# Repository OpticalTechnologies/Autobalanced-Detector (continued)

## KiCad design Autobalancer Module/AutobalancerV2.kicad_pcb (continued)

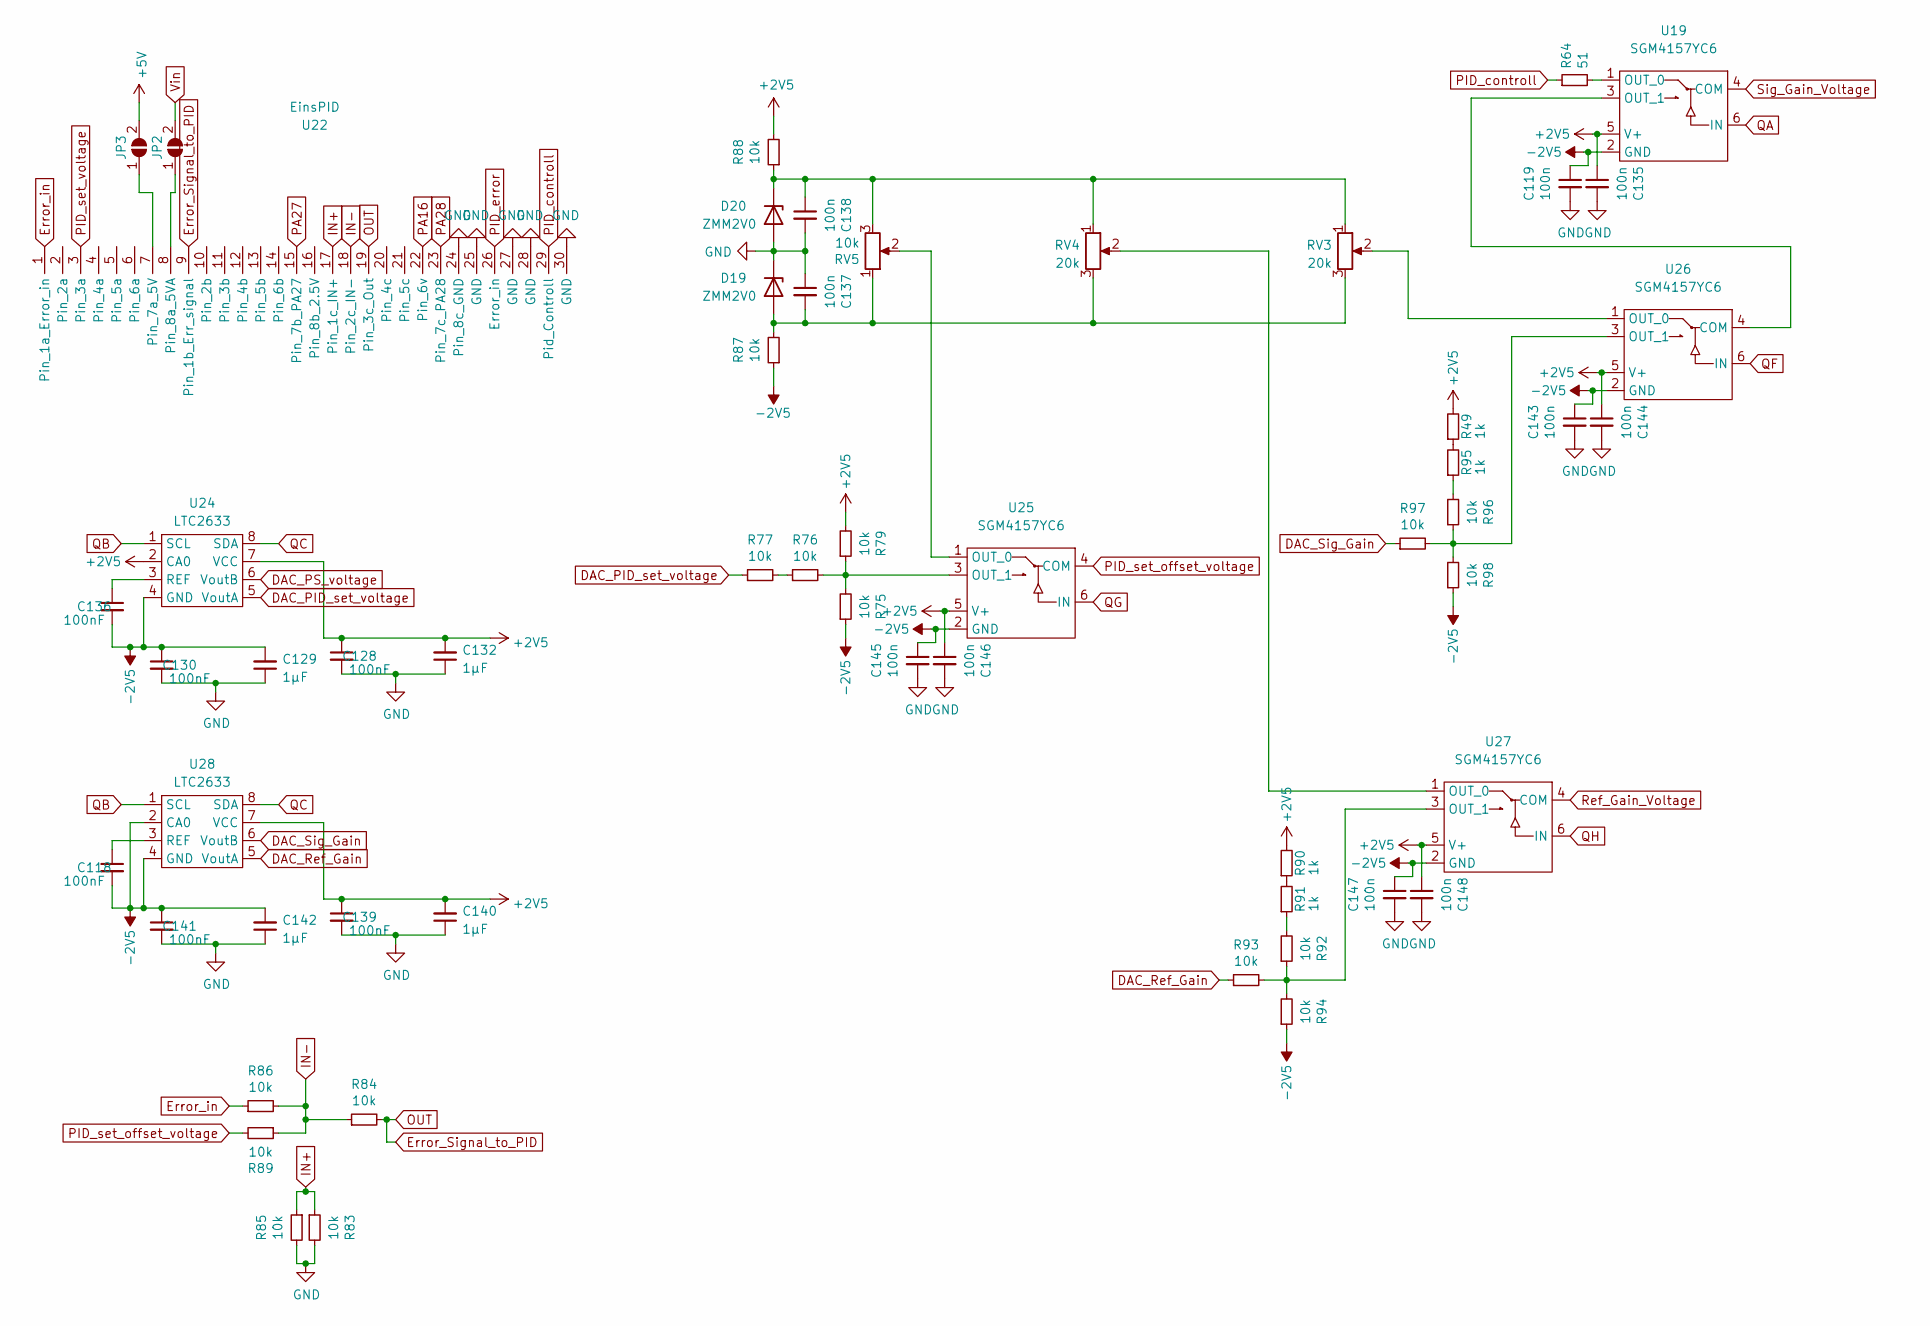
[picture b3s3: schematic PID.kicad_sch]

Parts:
C118, C128, C130, C136, C139, C141: 100nF; C_0402_1005Metric; LCSC C307331
C119, C135, C137, C138, C143, C144, C145, C146, C147, C148: 100n; C_0402_1005Metric; LCSC C1525
C129, C132, C140, C142: 1µF; C_0402_1005Metric; LCSC C52923
D19, D20: ZMM2V0; D_MiniMELF; LCSC C8079
JP2, JP3: SolderJumper_2_Open; 0603_solderbridge
R49, R90, R91, R95: 1k; R_0402_1005Metric; LCSC C11702
R64: 51; R_0402_1005Metric; LCSC C25125
R75, R76, R77, R79, R83, R84, R85, R86, R87, R88, R89, R92, R93, R94, R96, R97, R98: 10k; R_0402_1005Metric; LCSC C25744
RV3, RV4: 20k; Potentiometer_Bourns_3296W_Vertical
RV5: 10k; Potentiometer_Bourns_3296W_Vertical
U19, U25, U26, U27: SGM4157YC6; SC-60; LCSC C124895
U22: EinsPID
U24, U28: LTC2633; SOT-23-8

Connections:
+2V5: C128.1, C132.2, C135.1, C139.1, C140.2, C144.1, C146.1, C148.1, R49.2, R79.2, R88.2, R90.2, U19.5 (V+), U24.2 (CA0), U24.7 (VCC), U25.5 (V+), U26.5 (V+), U27.5 (V+), U28.7 (VCC); also elsewhere on the board
+5V: JP3.2 (B); also elsewhere on the board
-2V5: C118.2, C119.1, C129.2, C130.1, C136.2, C141.1, C142.2, C143.1, C145.1, C147.1, R75.1, R87.1, R94.1, R98.1, U19.2 (GND), U24.4 (GND), U25.2 (GND), U26.2 (GND), U27.2 (GND), U28.2 (CA0), U28.4 (GND); also elsewhere on the board
DAC_PID_set_voltage: R77.1, U24.5 (VoutA)
DAC_PS_voltage: U24.6 (VoutB); also elsewhere on the board
DAC_Ref_Gain: R93.1, U28.5 (VoutA)
DAC_Sig_Gain: R97.1, U28.6 (VoutB)
Error_Signal_to_PID: R84.2, U22.9 (Pin_1b_Err_signal), U22.19 (Pin_3c_Out)
Error_in: R86.1, U22.1 (Pin_1a_Error_in)
GND: C119.2, C128.2, C129.1, C130.2, C132.1, C135.2, C137.1, C138.2, C139.2, C140.1, C141.2, C142.1, C143.2, C144.2, C145.2, C146.2, C147.2, C148.2, D19.1 (K), D20.2 (A), R83.2, R85.2, U22.24 (Pin_8c_GND), U22.25 (GND), U22.27 (GND), U22.28 (GND), U22.30 (GND); also elsewhere on the board
IN+: R83.1, R85.1, U22.17 (Pin_1c_IN+)
IN-: R84.1, R86.2, R89.1, U22.18 (Pin_2c_IN-)
unnamed: C118.1, U28.3 (REF)
unnamed: C136.1, U24.3 (REF)
unnamed: C137.2, D19.2 (A), R87.2, RV3.3, RV4.3, RV5.1
unnamed: C138.1, D20.1 (K), R88.1, RV3.1, RV4.1, RV5.3
unnamed: JP2.1 (A), U22.8 (Pin_8a_5VA)
unnamed: JP3.1 (A), U22.7 (Pin_7a_5V)
unnamed: R49.1, R95.2
unnamed: R64.2, U19.1 (OUT_0)
unnamed: R75.2, R76.2, R79.1, U25.3 (OUT_1)
unnamed: R76.1, R77.2
unnamed: R90.1, R91.2
unnamed: R91.1, R92.2
unnamed: R92.1, R93.2, R94.2, U27.3 (OUT_1)
unnamed: R95.1, R96.2
unnamed: R96.1, R97.2, R98.2, U26.3 (OUT_1)
unnamed: RV3.2, U26.1 (OUT_0)
unnamed: RV4.2, U27.1 (OUT_0)
unnamed: RV5.2, U25.1 (OUT_0)
unnamed: U19.3 (OUT_1), U26.4 (COM)
PA16: U22.22 (Pin_6v); also elsewhere on the board
PA27: U22.15 (Pin_7b_PA27); also elsewhere on the board
PA28: U22.23 (Pin_7c_PA28); also elsewhere on the board
PID_controll: R64.1, U22.29 (Pid_Controll)
PID_error: U22.26 (Error_in); also elsewhere on the board
PID_set_offset_voltage: R89.2, U25.4 (COM)
PID_set_voltage: U22.3 (Pin_3a)
QA: U19.6 (IN); also elsewhere on the board
QB: U24.1 (SCL), U28.1 (SCL); also elsewhere on the board
QC: U24.8 (SDA), U28.8 (SDA); also elsewhere on the board
QF: U26.6 (IN); also elsewhere on the board
QG: U25.6 (IN); also elsewhere on the board
QH: U27.6 (IN); also elsewhere on the board
Ref_Gain_Voltage: U27.4 (COM); also elsewhere on the board
Sig_Gain_Voltage: U19.4 (COM); also elsewhere on the board
Vin: JP2.2 (B); also elsewhere on the board

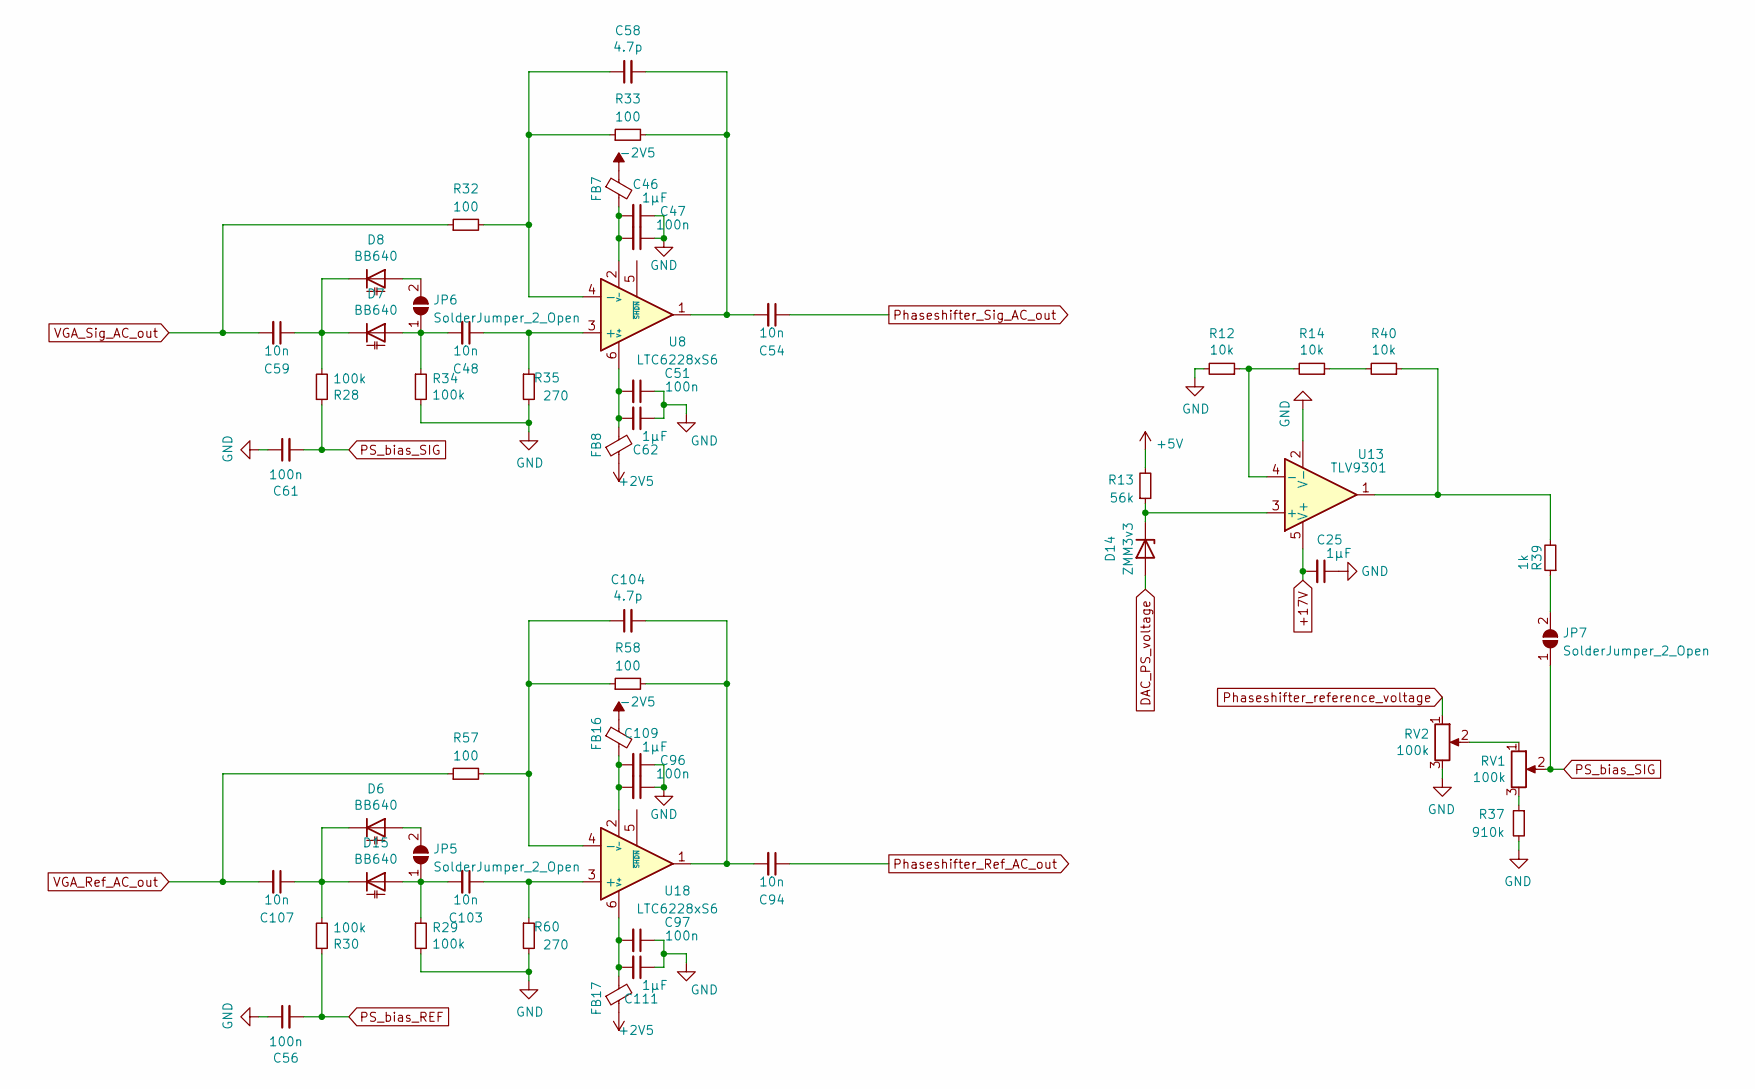
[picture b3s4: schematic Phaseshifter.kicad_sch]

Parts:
C25, C46, C62, C109, C111: 1µF; C_0402_1005Metric; LCSC C52923
C47, C51, C56, C61, C96, C97: 100n; C_0402_1005Metric; LCSC C1525
C48, C54, C59, C94, C103, C107: 10n; C_0402_1005Metric; LCSC C15195
C58, C104: 4.7p; C_0402_1005Metric; LCSC C1569
D6, D7, D8, D15: BB640; D_SOD-323F; LCSC C150932
D14: ZMM3v3; D_MiniMELF; LCSC C8056
FB7, FB8, FB16, FB17: Ferrite_Bead_Small; L_0603_1608Metric; LCSC C1002
JP5, JP6, JP7: SolderJumper_2_Open; 0603_solderbridge
R12, R14, R40: 10k; R_0402_1005Metric; LCSC C25744
R13: 56k; R_0402_1005Metric; LCSC C25796
R28, R29, R30, R34: 100k; R_0402_1005Metric; LCSC C25741
R32, R33, R57, R58: 100; R_0402_1005Metric; LCSC C25076
R35, R60: 270; R_0402_1005Metric; LCSC C25099
R37: 910k; R_0402_1005Metric; LCSC C25572
R39: 1k; R_0402_1005Metric; LCSC C11702
RV1, RV2: 100k; Potentiometer_Bourns_3296W_Vertical
U8, U18: LTC6228xS6; TSOT-23-6
U13: TLV9301; SOT-23-5; Mouser 595-TLV9301IDBVR

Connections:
+2V5: FB8.1, FB17.1; also elsewhere on the board
+5V: R13.2; also elsewhere on the board
+17V: C25.2, U13.5 (V+); also elsewhere on the board
-2V5: FB7.1, FB16.1; also elsewhere on the board
DAC_PS_voltage: D14.2 (A); also elsewhere on the board
GND: C25.1, C46.1, C47.1, C51.1, C56.1, C61.1, C62.1, C96.1, C97.1, C109.1, C111.1, R12.2, R29.2, R34.2, R35.2, R37.2, R60.2, RV2.3, U13.2 (V-); also elsewhere on the board
unnamed: C46.2, C47.2, FB7.2, U8.2 (V-)
unnamed: C48.1, R35.1, U8.3 (+)
unnamed: C48.2, D7.2 (A), JP6.1 (A), R34.1
unnamed: C51.2, C62.2, FB8.2, U8.6 (V+)
unnamed: C54.2, C58.2, R33.2, U8.1
unnamed: C58.1, R32.2, R33.1, U8.4 (-)
unnamed: C59.1, D7.1 (K), D8.1 (K), R28.2
unnamed: C103.1, R60.1, U18.3 (+)
unnamed: C103.2, D15.2 (A), JP5.1 (A), R29.1
unnamed: C104.1, R57.2, R58.1, U18.4 (-)
unnamed: C94.2, C104.2, R58.2, U18.1
unnamed: C107.1, D6.1 (K), D15.1 (K), R30.2
unnamed: C96.2, C109.2, FB16.2, U18.2 (V-)
unnamed: C97.2, C111.2, FB17.2, U18.6 (V+)
unnamed: D6.2 (A), JP5.2 (B)
unnamed: D8.2 (A), JP6.2 (B)
unnamed: D14.1 (K), R13.1, U13.3 (+)
unnamed: JP7.2 (B), R39.1
unnamed: R12.1, R14.2, U13.4 (-)
unnamed: R14.1, R40.2
unnamed: R37.1, RV1.3
unnamed: R39.2, R40.1, U13.1
unnamed: RV1.1, RV2.2
PS_bias_REF: C56.2, R30.1; also elsewhere on the board
PS_bias_SIG: C61.2, JP7.1 (A), R28.1, RV1.2
Phaseshifter_Ref_AC_out: C94.1; also elsewhere on the board
Phaseshifter_Sig_AC_out: C54.1; also elsewhere on the board
Phaseshifter_reference_voltage: RV2.1; also elsewhere on the board
VGA_Ref_AC_out: C107.2, R57.1; also elsewhere on the board
VGA_Sig_AC_out: C59.2, R32.1; also elsewhere on the board

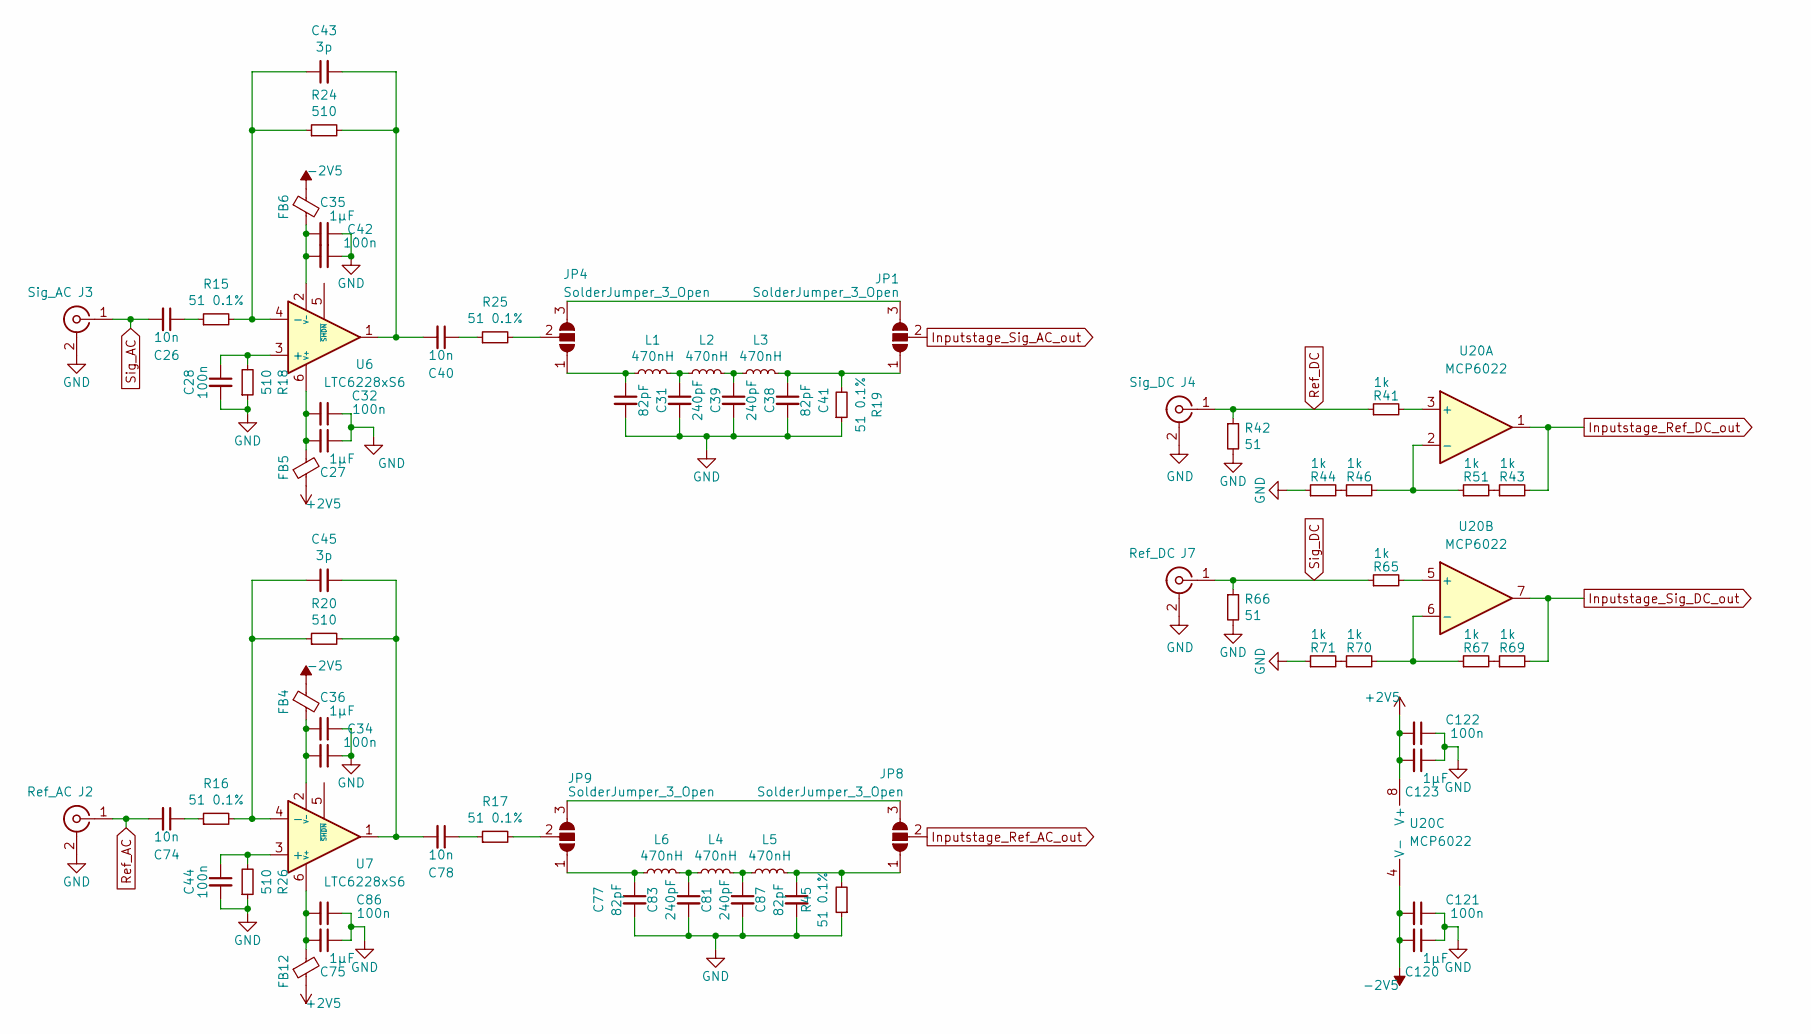
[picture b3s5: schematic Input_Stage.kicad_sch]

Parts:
C26, C40, C74, C78: 10n; C_0402_1005Metric; LCSC C15195
C27, C35, C36, C75, C120, C123: 1µF; C_0402_1005Metric; LCSC C52923
C28, C32, C34, C42, C44, C86, C121, C122: 100n; C_0402_1005Metric; LCSC C1525
C31, C41, C77, C87: 82pF; C_0402_1005Metric; LCSC C162123
C38, C39, C81, C83: 240pF; C_0603_1608Metric; LCSC C519400
C43, C45: 3p; C_0402_1005Metric; LCSC C88891
FB4, FB5, FB6, FB12: Ferrite_Bead_Small; L_0603_1608Metric; LCSC C1002
J2: Ref_AC; SMA_edge
J3: Sig_AC; SMA_edge
J4: Sig_DC; SMA_edge
J7: Ref_DC; SMA_edge
JP1, JP4, JP8, JP9: SolderJumper_3_Open; 0603_solderbridge3
L1, L2, L3, L4, L5, L6: 470nH; AISC-0805_Inductor; LCSC C127457
R15, R16, R17, R19, R25, R45: 51 0.1%; R_0402_1005Metric; LCSC C445570
R18, R20, R24, R26: 510; R_0402_1005Metric; LCSC C25170
R41, R43, R44, R46, R51, R65, R67, R69, R70, R71: 1k; R_0402_1005Metric; LCSC C11702
R42, R66: 51; R_0402_1005Metric; LCSC C25125
U6, U7: LTC6228xS6; TSOT-23-6
U20: MCP6022; SOIC-8_3.9x4.9mm_P1.27mm; LCSC C57639

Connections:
+2V5: C122.2, C123.2, FB5.1, FB12.1, U20.8 (V+); also elsewhere on the board
-2V5: C120.2, C121.2, FB4.1, FB6.1, U20.4 (V-); also elsewhere on the board
GND: C27.1, C28.2, C31.2, C32.1, C34.1, C35.1, C36.1, C38.2, C39.2, C41.2, C42.1, C44.2, C75.1, C77.2, C81.2, C83.2, C86.1, C87.2, C120.1, C121.1, C122.1, C123.1, J2.2 (Ext), J3.2 (Ext), J4.2 (Ext), J7.2 (Ext), R18.1, R19.1, R26.1, R42.2, R44.1, R45.1, R66.2, R71.1; also elsewhere on the board
Inputstage_Ref_AC_out: JP8.2 (C); also elsewhere on the board
Inputstage_Ref_DC_out: R43.2, U20.1; also elsewhere on the board
Inputstage_Sig_AC_out: JP1.2 (C); also elsewhere on the board
Inputstage_Sig_DC_out: R69.2, U20.7; also elsewhere on the board
unnamed: C26.1, R15.1
unnamed: C27.2, C32.2, FB5.2, U6.6 (V+)
unnamed: C28.1, R18.2, U6.3 (+)
unnamed: C31.1, JP4.1 (A), L1.1
unnamed: C34.2, C36.2, FB4.2, U7.2 (V-)
unnamed: C35.2, C42.2, FB6.2, U6.2 (V-)
unnamed: C38.1, L2.2, L3.1
unnamed: C39.1, L1.2, L2.1
unnamed: C40.1, R25.1
unnamed: C40.2, C43.2, R24.2, U6.1
unnamed: C41.1, JP1.1 (A), L3.2, R19.2
unnamed: C43.1, R15.2, R24.1, U6.4 (-)
unnamed: C44.1, R26.2, U7.3 (+)
unnamed: C45.1, R16.2, R20.1, U7.4 (-)
unnamed: C45.2, C78.2, R20.2, U7.1
unnamed: C74.1, R16.1
unnamed: C75.2, C86.2, FB12.2, U7.6 (V+)
unnamed: C77.1, JP9.1 (A), L6.2
unnamed: C78.1, R17.1
unnamed: C81.1, L4.1, L5.2
unnamed: C83.1, L4.2, L6.1
unnamed: C87.1, JP8.1 (A), L5.1, R45.2
unnamed: JP1.3 (B), JP4.3 (B)
unnamed: JP4.2 (C), R25.2
unnamed: JP8.3 (B), JP9.3 (B)
unnamed: JP9.2 (C), R17.2
unnamed: R41.2, U20.3 (+)
unnamed: R43.1, R51.2
unnamed: R44.2, R46.1
unnamed: R46.2, R51.1, U20.2 (-)
unnamed: R65.2, U20.5 (+)
unnamed: R67.1, R70.2, U20.6 (-)
unnamed: R67.2, R69.1
unnamed: R70.1, R71.2
Ref_AC: C74.2, J2.1 (In)
Ref_DC: J4.1 (In), R41.1, R42.1
Sig_AC: C26.2, J3.1 (In)
Sig_DC: J7.1 (In), R65.1, R66.1

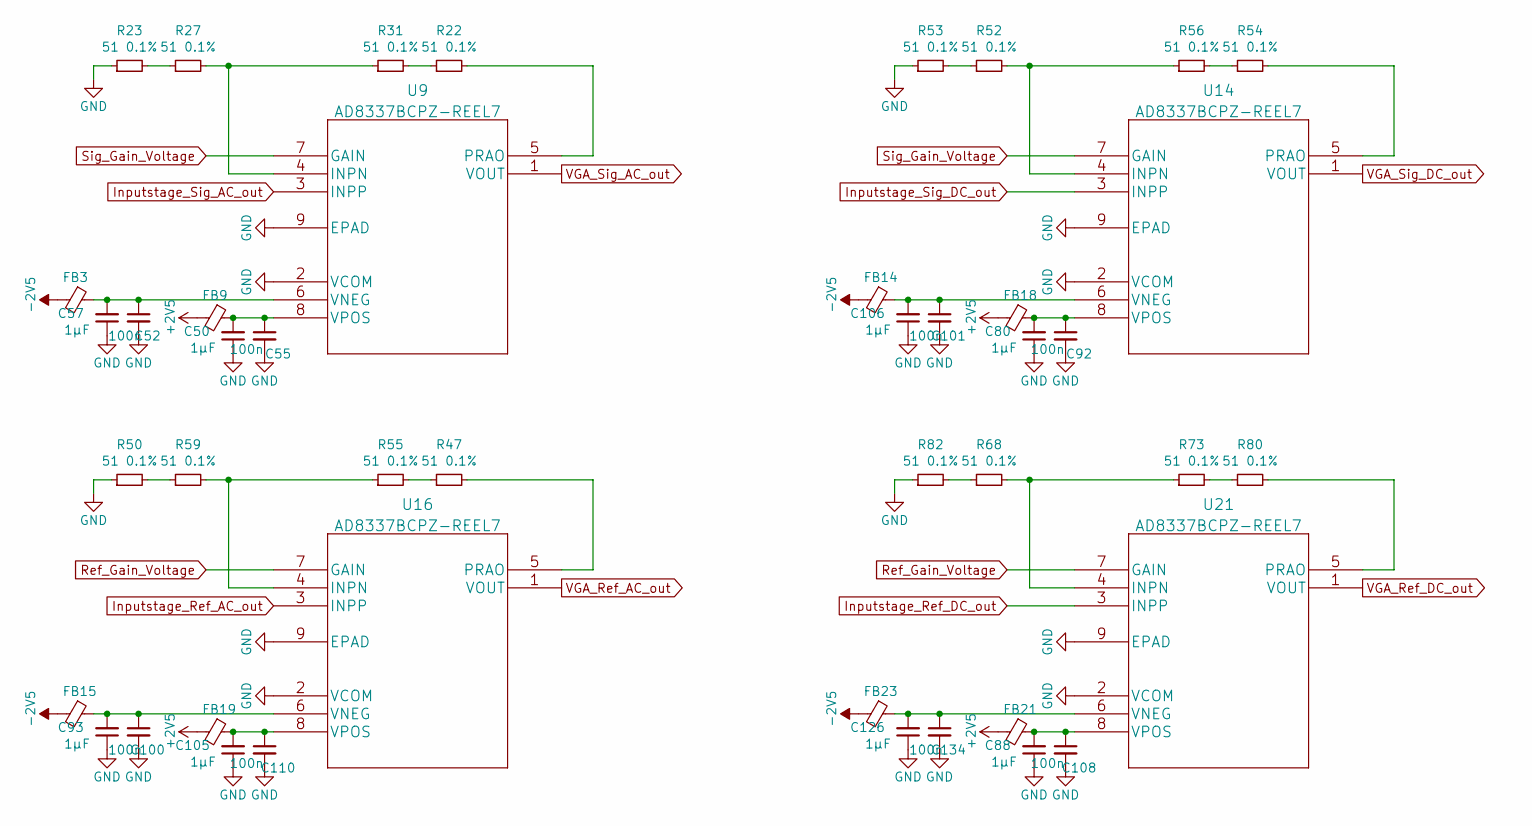
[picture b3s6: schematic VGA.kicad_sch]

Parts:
C50, C57, C80, C88, C93, C105, C106, C126: 1µF; C_0402_1005Metric; LCSC C52923
C52, C55, C92, C100, C101, C108, C110, C134: 100n; C_0402_1005Metric; LCSC C1525
FB3, FB9, FB14, FB15, FB18, FB19, FB21, FB23: Ferrite_Bead_Small; L_0603_1608Metric; LCSC C1002
R22, R23, R27, R31, R47, R50, R52, R53, R54, R55, R56, R59, R68, R73, R80, R82: 51 0.1%; R_0402_1005Metric; LCSC C445570
U9, U14, U16, U21: AD8337BCPZ-REEL7; LFCSP-8-1EP_3x3mm_P0.5mm_EP1.45x1.74mm

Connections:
+2V5: FB9.2, FB18.2, FB19.2, FB21.2; also elsewhere on the board
-2V5: FB3.2, FB14.2, FB15.2, FB23.2; also elsewhere on the board
GND: C50.1, C52.2, C55.2, C57.1, C80.1, C88.1, C92.2, C93.1, C100.2, C101.2, C105.1, C106.1, C108.2, C110.2, C126.1, C134.2, R23.1, R50.1, R53.1, R82.1, U9.2 (VCOM), U9.9 (EPAD), U14.2 (VCOM), U14.9 (EPAD), U16.2 (VCOM), U16.9 (EPAD), U21.2 (VCOM), U21.9 (EPAD); also elsewhere on the board
Inputstage_Ref_AC_out: U16.3 (INPP); also elsewhere on the board
Inputstage_Ref_DC_out: U21.3 (INPP); also elsewhere on the board
Inputstage_Sig_AC_out: U9.3 (INPP); also elsewhere on the board
Inputstage_Sig_DC_out: U14.3 (INPP); also elsewhere on the board
unnamed: C50.2, C55.1, FB9.1, U9.8 (VPOS)
unnamed: C52.1, C57.2, FB3.1, U9.6 (VNEG)
unnamed: C80.2, C92.1, FB18.1, U14.8 (VPOS)
unnamed: C93.2, C100.1, FB15.1, U16.6 (VNEG)
unnamed: C101.1, C106.2, FB14.1, U14.6 (VNEG)
unnamed: C105.2, C110.1, FB19.1, U16.8 (VPOS)
unnamed: C88.2, C108.1, FB21.1, U21.8 (VPOS)
unnamed: C126.2, C134.1, FB23.1, U21.6 (VNEG)
unnamed: R22.1, R31.2
unnamed: R22.2, U9.5 (PRAO)
unnamed: R23.2, R27.1
unnamed: R27.2, R31.1, U9.4 (INPN)
unnamed: R47.1, R55.2
unnamed: R47.2, U16.5 (PRAO)
unnamed: R50.2, R59.1
unnamed: R52.1, R53.2
unnamed: R52.2, R56.1, U14.4 (INPN)
unnamed: R54.1, R56.2
unnamed: R54.2, U14.5 (PRAO)
unnamed: R55.1, R59.2, U16.4 (INPN)
unnamed: R68.1, R82.2
unnamed: R68.2, R73.1, U21.4 (INPN)
unnamed: R73.2, R80.1
unnamed: R80.2, U21.5 (PRAO)
Ref_Gain_Voltage: U16.7 (GAIN), U21.7 (GAIN); also elsewhere on the board
Sig_Gain_Voltage: U9.7 (GAIN), U14.7 (GAIN); also elsewhere on the board
VGA_Ref_AC_out: U16.1 (VOUT); also elsewhere on the board
VGA_Ref_DC_out: U21.1 (VOUT); also elsewhere on the board
VGA_Sig_AC_out: U9.1 (VOUT); also elsewhere on the board
VGA_Sig_DC_out: U14.1 (VOUT); also elsewhere on the board

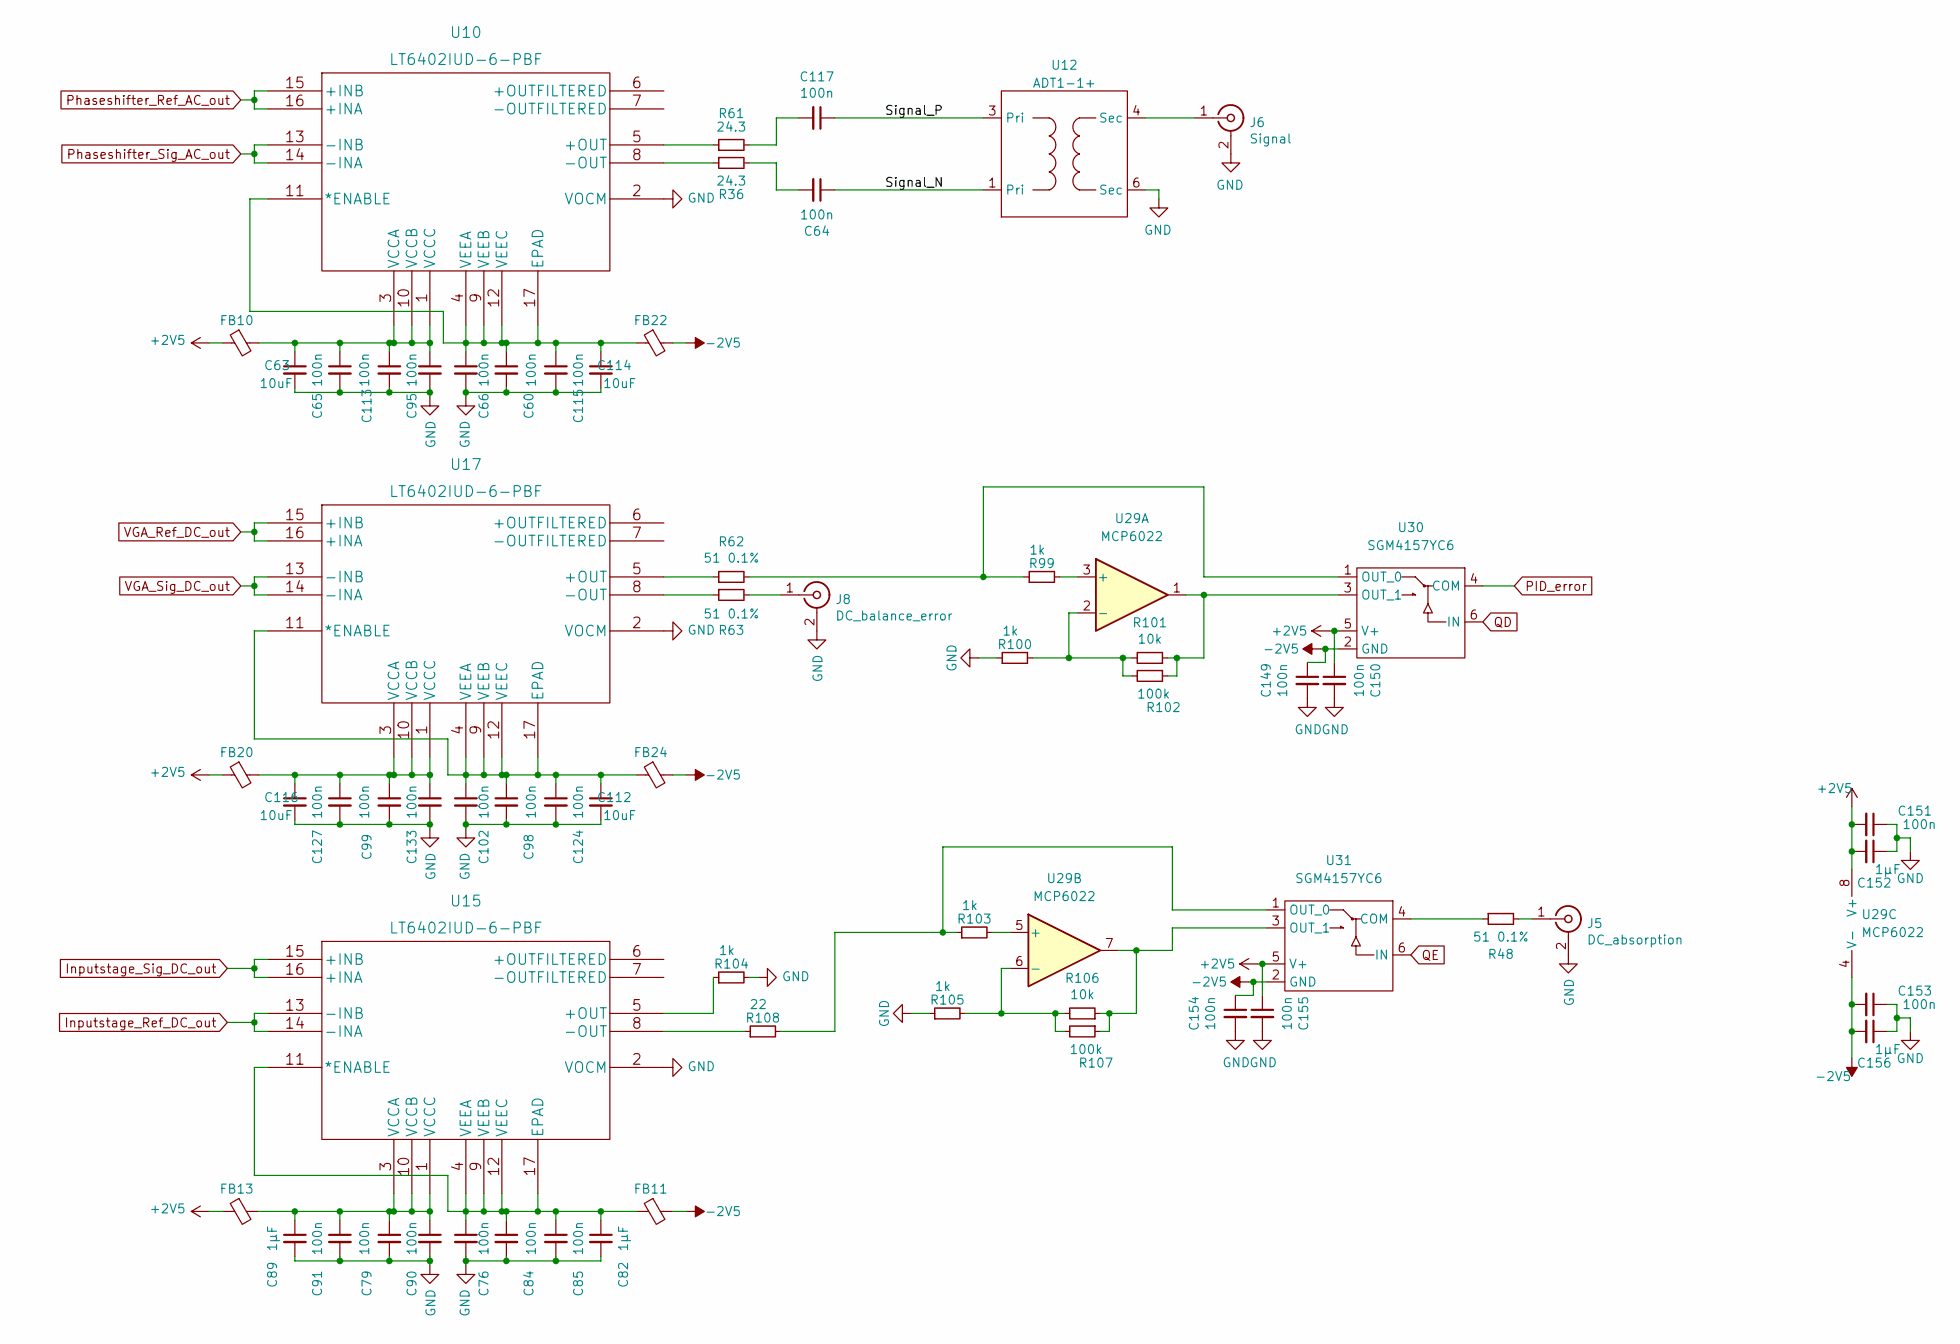
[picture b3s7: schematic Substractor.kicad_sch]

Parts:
C60, C64, C65, C66, C76, C79, C84, C85, C90, C91, C95, C98, C99, C102, C113, C115, C117, C124, C127, C133, C149, C150, C151, C153, C154, C155: 100n; C_0402_1005Metric; LCSC C1525
C63, C112, C114, C116: 10uF; C_1206_3216Metric; LCSC C13585
C82, C89, C152, C156: 1µF; C_0402_1005Metric; LCSC C52923
FB10, FB11, FB13, FB20, FB22, FB24: Ferrite_Bead_Small; L_0603_1608Metric; LCSC C1002
J5: DC_absorption; SMA_edge
J6: Signal; SMA_edge
J8: DC_balance_error; SMA_edge
R36, R61: 24.3; R_0402_1005Metric; LCSC C321400
R48, R62, R63: 51 0.1%; R_0402_1005Metric; LCSC C445570
R99, R100, R103, R104, R105: 1k; R_0402_1005Metric; LCSC C11702
R101, R106: 10k; R_0402_1005Metric; LCSC C25744
R102, R107: 100k; R_0402_1005Metric; LCSC C25741
R108: 22; R_0402_1005Metric
U10, U15, U17: LT6402IUD-6-PBF; QFN-16-1EP_3x3mm_P0.5mm_EP1.45x1.45mm_ThermalVias
U12: ADT1-1+; JLCPCB C2683432
U29: MCP6022; SOIC-8_3.9x4.9mm_P1.27mm; LCSC C57639
U30, U31: SGM4157YC6; SC-60; LCSC C124895

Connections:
+2V5: C150.1, C151.2, C152.2, C155.1, FB10.1, FB13.1, FB20.1, U29.8 (V+), U30.5 (V+), U31.5 (V+); also elsewhere on the board
-2V5: C149.1, C153.2, C154.1, C156.2, FB11.2, FB22.2, FB24.2, U29.4 (V-), U30.2 (GND), U31.2 (GND); also elsewhere on the board
/Substractor/Signal_N: C64.1, U12.1 (Pri)
/Substractor/Signal_P: C117.1, U12.3 (Pri)
GND: C60.2, C63.2, C65.2, C66.2, C76.2, C79.2, C82.2, C84.2, C85.2, C89.2, C90.2, C91.2, C95.2, C98.2, C99.2, C102.2, C112.2, C113.2, C114.2, C115.2, C116.2, C124.2, C127.2, C133.2, C149.2, C150.2, C151.1, C152.1, C153.1, C154.2, C155.2, C156.1, J5.2 (Ext), J6.2 (Ext), J8.2 (Ext), R100.1, R104.2, R105.1, U10.2 (VOCM), U12.6 (Sec), U15.2 (VOCM), U17.2 (VOCM); also elsewhere on the board
Inputstage_Ref_DC_out: U15.13 (-INB), U15.14 (-INA); also elsewhere on the board
Inputstage_Sig_DC_out: U15.15 (+INB), U15.16 (+INA); also elsewhere on the board
unnamed: C64.2, R36.2
unnamed: C76.1, C82.1, C84.1, C85.1, FB11.1, U15.4 (VEEA), U15.9 (VEEB), U15.11 (*ENABLE), U15.12 (VEEC), U15.17 (EPAD)
unnamed: C79.1, C89.1, C90.1, C91.1, FB13.2, U15.1 (VCCC), U15.3 (VCCA), U15.10 (VCCB)
unnamed: C98.1, C102.1, C112.1, C124.1, FB24.1, U17.4 (VEEA), U17.9 (VEEB), U17.11 (*ENABLE), U17.12 (VEEC), U17.17 (EPAD)
unnamed: C63.1, C65.1, C95.1, C113.1, FB10.2, U10.1 (VCCC), U10.3 (VCCA), U10.10 (VCCB)
unnamed: C60.1, C66.1, C114.1, C115.1, FB22.1, U10.4 (VEEA), U10.9 (VEEB), U10.11 (*ENABLE), U10.12 (VEEC), U10.17 (EPAD)
unnamed: C99.1, C116.1, C127.1, C133.1, FB20.2, U17.1 (VCCC), U17.3 (VCCA), U17.10 (VCCB)
unnamed: C117.2, R61.2
unnamed: J5.1 (In), R48.2
unnamed: J6.1 (In), U12.4 (Sec)
unnamed: J8.1 (In), R63.2
unnamed: R36.1, U10.8 (-OUT)
unnamed: R48.1, U31.4 (COM)
unnamed: R61.1, U10.5 (+OUT)
unnamed: R62.1, U17.5 (+OUT)
unnamed: R62.2, R99.1, U30.1 (OUT_0)
unnamed: R63.1, U17.8 (-OUT)
unnamed: R99.2, U29.3 (+)
unnamed: R100.2, R101.2, R102.2, U29.2 (-)
unnamed: R101.1, R102.1, U29.1, U30.3 (OUT_1)
unnamed: R103.1, R108.2, U31.1 (OUT_0)
unnamed: R103.2, U29.5 (+)
unnamed: R105.2, R106.2, R107.2, U29.6 (-)
unnamed: R106.1, R107.1, U29.7, U31.3 (OUT_1)
unnamed: R104.1, U15.5 (+OUT)
unnamed: R108.1, U15.8 (-OUT)
PID_error: U30.4 (COM); also elsewhere on the board
Phaseshifter_Ref_AC_out: U10.15 (+INB), U10.16 (+INA); also elsewhere on the board
Phaseshifter_Sig_AC_out: U10.13 (-INB), U10.14 (-INA); also elsewhere on the board
QD: U30.6 (IN); also elsewhere on the board
QE: U31.6 (IN); also elsewhere on the board
VGA_Ref_DC_out: U17.15 (+INB), U17.16 (+INA); also elsewhere on the board
VGA_Sig_DC_out: U17.13 (-INB), U17.14 (-INA); also elsewhere on the board

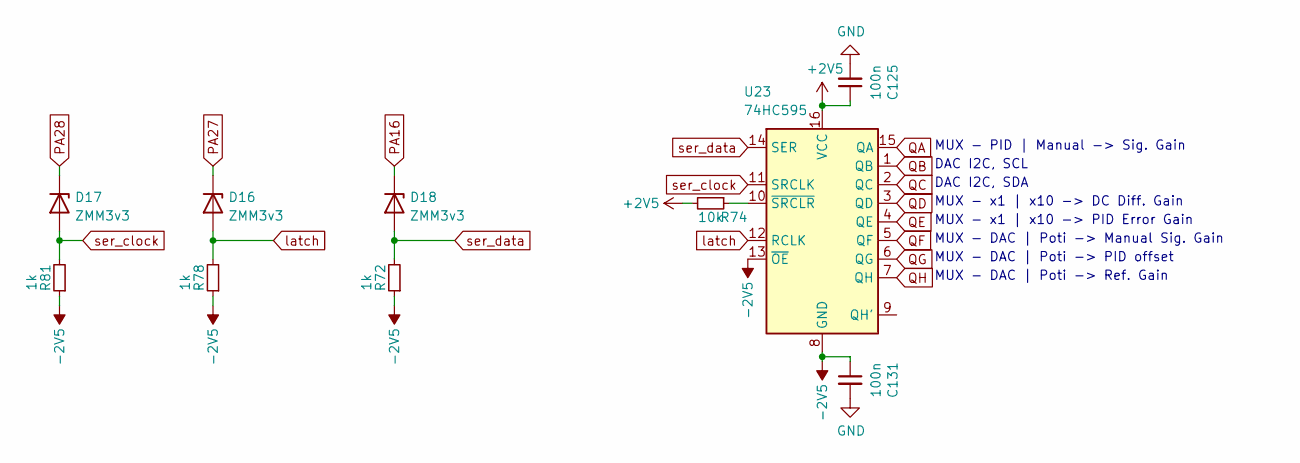
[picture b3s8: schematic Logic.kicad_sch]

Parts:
C125, C131: 100n; C_0402_1005Metric; LCSC C1525
D16, D17, D18: ZMM3v3; D_MiniMELF; LCSC C8056
R72, R78, R81: 1k; R_0402_1005Metric; LCSC C11702
R74: 10k; R_0402_1005Metric; LCSC C25744
U23: 74HC595; SOIC-16_3.9x9.9mm_P1.27mm; LCSC C5947

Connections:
+2V5: C125.1, R74.2, U23.16 (VCC); also elsewhere on the board
-2V5: C131.1, R72.1, R78.1, R81.1, U23.8 (GND), U23.13 (~OE); also elsewhere on the board
GND: C125.2, C131.2; also elsewhere on the board
unnamed: R74.1, U23.10 (~SRCLR)
PA16: D18.1 (K); also elsewhere on the board
PA27: D16.1 (K); also elsewhere on the board
PA28: D17.1 (K); also elsewhere on the board
QA: U23.15 (QA); also elsewhere on the board
QB: U23.1 (QB); also elsewhere on the board
QC: U23.2 (QC); also elsewhere on the board
QD: U23.3 (QD); also elsewhere on the board
QE: U23.4 (QE); also elsewhere on the board
QF: U23.5 (QF); also elsewhere on the board
QG: U23.6 (QG); also elsewhere on the board
QH: U23.7 (QH); also elsewhere on the board
latch: D16.2 (A), R78.2, U23.12 (RCLK)
ser_clock: D17.2 (A), R81.2, U23.11 (SRCLK)
ser_data: D18.2 (A), R72.2, U23.14 (SER)

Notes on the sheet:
MUX - DAC | Poti -> Ref. Gain
MUX - x1 | x10 -> DC Diff. Gain
MUX - PID | Manual -> Sig. Gain
MUX - DAC | Poti -> PID offset
MUX - x1 | x10 -> PID Error Gain
DAC I2C, SCL
DAC I2C, SDA
MUX - DAC | Poti -> Manual Sig. Gain
